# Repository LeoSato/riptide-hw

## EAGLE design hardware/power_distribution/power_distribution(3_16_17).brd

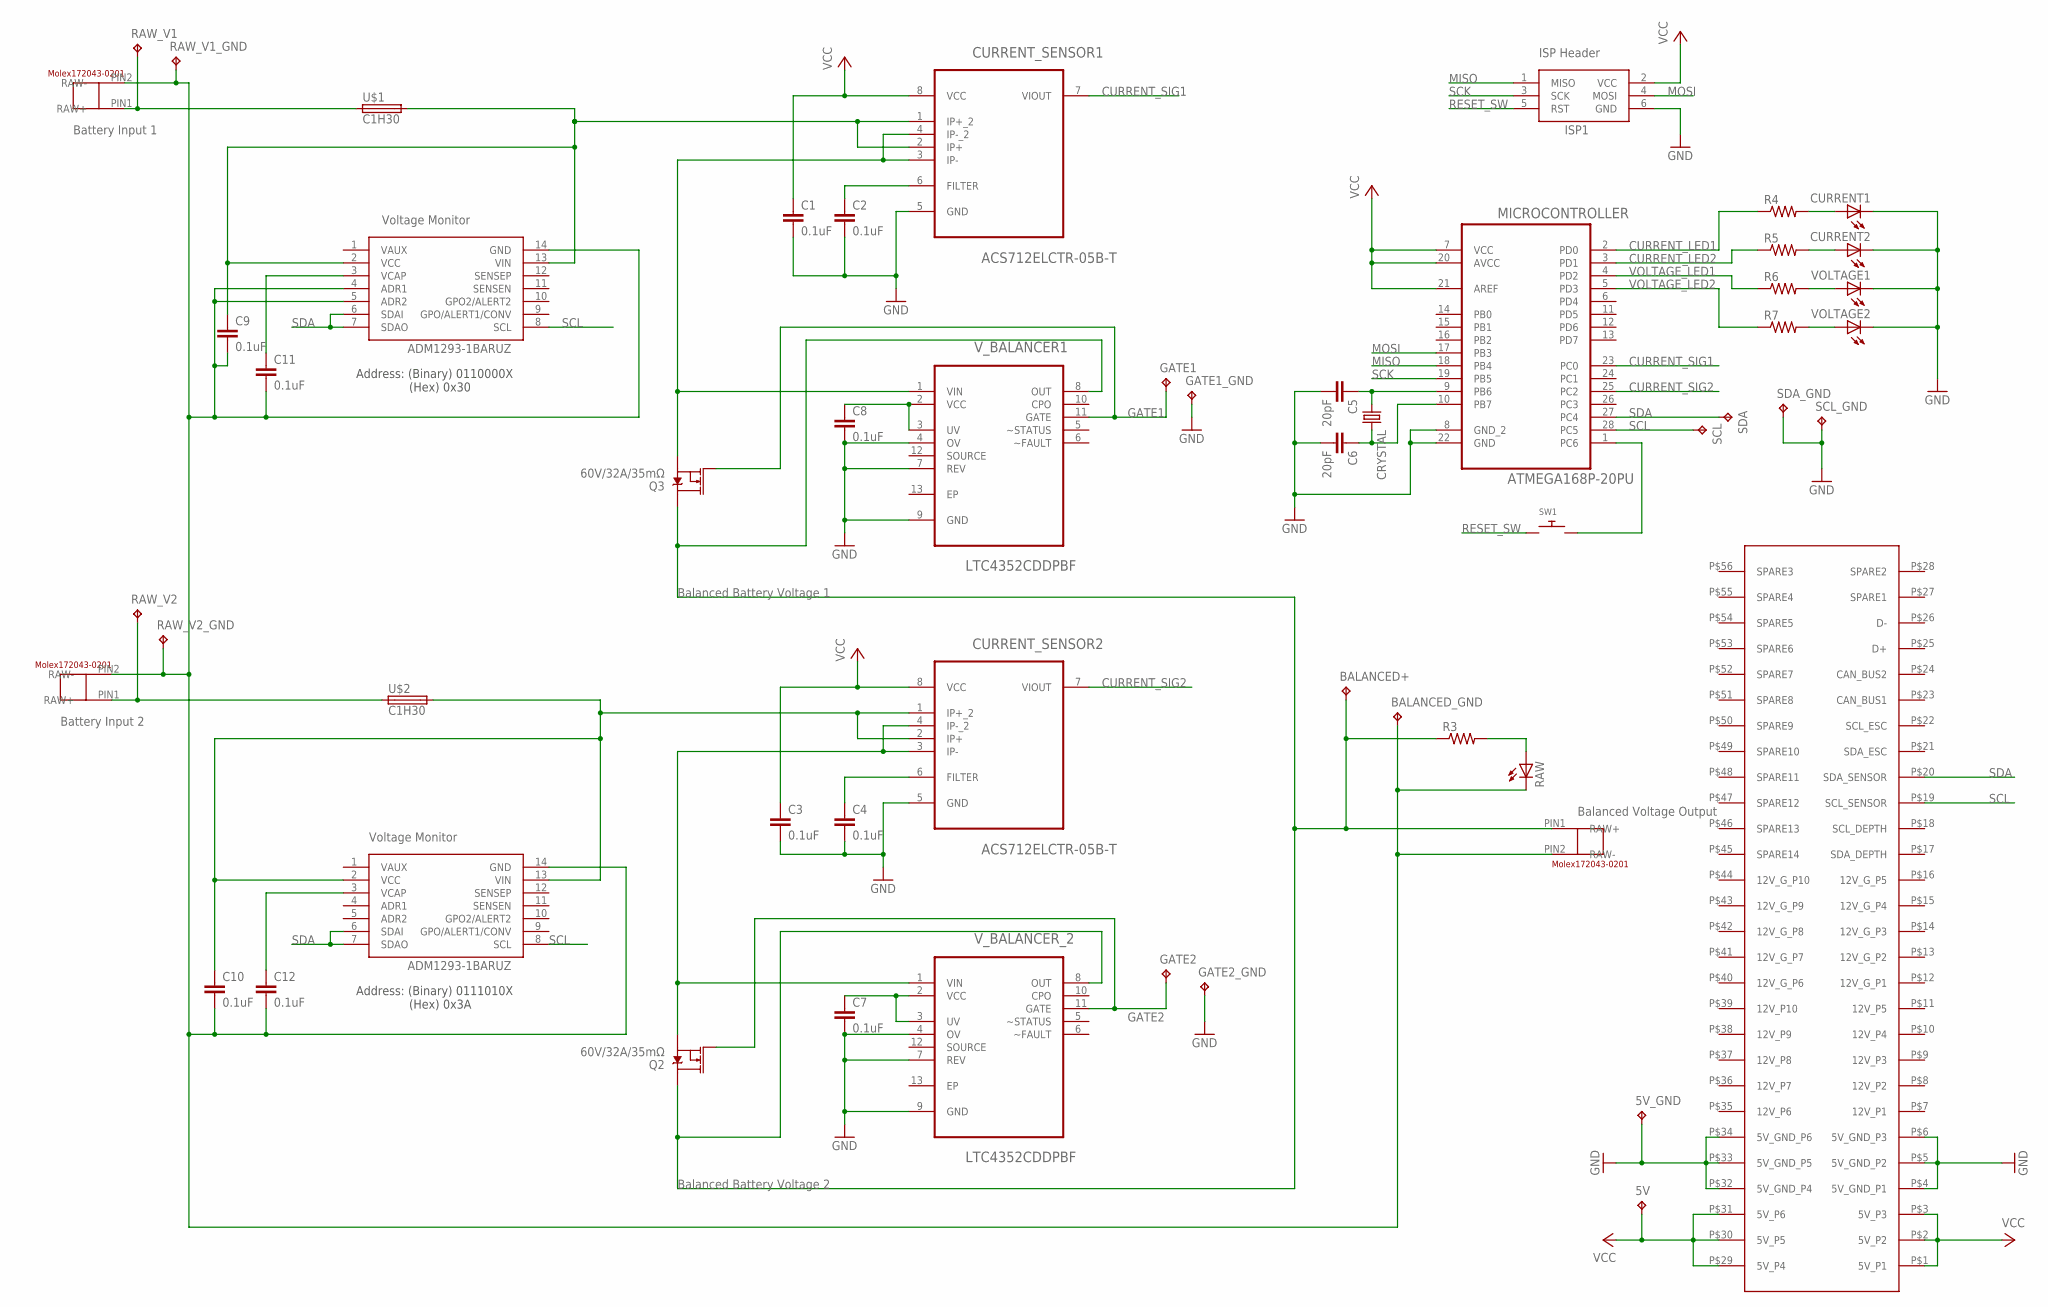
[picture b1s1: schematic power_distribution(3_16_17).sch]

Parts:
5V, 5V_GND: TPPAD1-13; P1-13
BALANCED+: TPPAD1-13; P1-13
BALANCED_GND: TPPAD1-13; P1-13
C1, C2, C3, C4, C7, C8, C9, C10, C11, C12: 0.1uF; CAP-PTH-SMALL-KIT
C5, C6: 20pF; CAP-PTH-SMALL-KIT
CRYSTAL: CRYSTALHC49U-V; HC49U-V
CURRENT1, CURRENT2: LED3MM
CURRENT_SENSOR1, CURRENT_SENSOR2: ACS712ELCTR-05B-T; SOIC127P600X175-8N
GATE1, GATE1_GND, GATE2, GATE2_GND: TPPAD1-13; P1-13
INPUT1, INPUT2: MOLEX172043-0201
ISP1: AVRISP-6; AVRISP
MICROCONTROLLER: ATMEGA168P-20PU; DIP254P762X457-28
OUTPUT: MOLEX172043-0201
Q2, Q3: 60V/32A/35mΩ; TO220V
R3, R4, R5, R6, R7: R-US_0207/12; 0207/12
RAW: LED3MM
RAW_V1, RAW_V1_GND, RAW_V2, RAW_V2_GND: TPPAD1-13; P1-13
SCL: TPPAD1-13; P1-13
SCL_GND: TPPAD1-13; P1-13
SDA: TPPAD1-13; P1-13
SDA_GND: TPPAD1-13; P1-13
SW1: SWITCH_PUSHBUTTONEVQ-PE; TACT_PANA-EVQ
U$1, U$2: C1H30
U$3: 1-530844-7
U$4, U$5: ADM1293; SOP65P640X120-14N
VOLTAGE1, VOLTAGE2: LED3MM
V_BALANCER1: LTC4352CDDPBF; DFN300X300X80-13N
V_BALANCER_2: LTC4352CDDPBF; DFN300X300X80-13N

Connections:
CURRENT_LED1: MICROCONTROLLER.2 (PD0), R4.1
CURRENT_LED2: MICROCONTROLLER.3 (PD1), R5.1
CURRENT_SIG1: CURRENT_SENSOR1.7 (VIOUT), MICROCONTROLLER.23 (PC0)
CURRENT_SIG2: CURRENT_SENSOR2.7 (VIOUT), MICROCONTROLLER.25 (PC2)
GATE1: GATE1.TP, Q3.1 (G), V_BALANCER1.11 (GATE)
GATE2: GATE2.TP, Q2.1 (G), V_BALANCER_2.11 (GATE)
GND: 5V_GND.TP, C1.2, C2.2, C3.2, C4.2, C5.2, C6.2, C7.2, C8.2, CURRENT1.K (C), CURRENT2.K (C), CURRENT_SENSOR1.5 (GND), CURRENT_SENSOR2.5 (GND), GATE1_GND.TP, GATE2_GND.TP, ISP1.6 (GND), MICROCONTROLLER.8 (GND_2), MICROCONTROLLER.22 (GND), SCL_GND.TP, SDA_GND.TP, U$3.P$4 (5V_GND_P1), U$3.P$5 (5V_GND_P2), U$3.P$6 (5V_GND_P3), U$3.P$32 (5V_GND_P4), U$3.P$33 (5V_GND_P5), U$3.P$34 (5V_GND_P6), VOLTAGE1.K (C), VOLTAGE2.K (C), V_BALANCER1.4 (OV), V_BALANCER1.7 (REV), V_BALANCER1.9 (GND), V_BALANCER_2.4 (OV), V_BALANCER_2.7 (REV), V_BALANCER_2.9 (GND)
MISO: ISP1.1 (MISO), MICROCONTROLLER.18 (PB4)
MOSI: ISP1.4 (MOSI), MICROCONTROLLER.17 (PB3)
unnamed: C9.1, CURRENT_SENSOR1.1 (IP+_2), CURRENT_SENSOR1.2 (IP+), U$1.P$2 (2), U$4.2 (VCC), U$4.13 (VIN)
unnamed: C5.1, CRYSTAL.1, MICROCONTROLLER.9 (PB6)
unnamed: C7.1, V_BALANCER_2.2 (VCC), V_BALANCER_2.3 (UV)
unnamed: C6.1, CRYSTAL.2, MICROCONTROLLER.10 (PB7)
unnamed: CURRENT_SENSOR1.3 (IP-), CURRENT_SENSOR1.4 (IP-_2), Q3.3 (S), V_BALANCER1.1 (VIN)
unnamed: CURRENT1.A, R4.2
unnamed: R3.2, RAW.A
unnamed: C8.1, V_BALANCER1.2 (VCC), V_BALANCER1.3 (UV)
unnamed: INPUT1.PIN1 (RAW+), RAW_V1.TP, U$1.P$1 (1)
unnamed: C10.1, CURRENT_SENSOR2.1 (IP+_2), CURRENT_SENSOR2.2 (IP+), U$2.P$2 (2), U$5.2 (VCC), U$5.13 (VIN)
unnamed: C11.1, U$4.3 (VCAP)
unnamed: CURRENT2.A, R5.2
unnamed: C2.1, CURRENT_SENSOR1.6 (FILTER)
unnamed: R6.2, VOLTAGE1.A
unnamed: INPUT2.PIN1 (RAW+), RAW_V2.TP, U$2.P$1 (1)
unnamed: R7.2, VOLTAGE2.A
unnamed: C4.1, CURRENT_SENSOR2.6 (FILTER)
unnamed: BALANCED_GND.TP, C9.2, C10.2, C11.2, C12.2, INPUT1.PIN2 (RAW-), INPUT2.PIN2 (RAW-), OUTPUT.PIN2 (RAW-), RAW.K (C), RAW_V1_GND.TP, RAW_V2_GND.TP, U$4.4 (ADR1), U$4.5 (ADR2), U$4.14 (GND), U$5.14 (GND)
unnamed: C12.1, U$5.3 (VCAP)
unnamed: BALANCED+.TP, OUTPUT.PIN1 (RAW+), Q2.2 (D), Q3.2 (D), R3.1, V_BALANCER1.8 (OUT), V_BALANCER_2.8 (OUT)
unnamed: MICROCONTROLLER.1 (PC6), SW1.P$2
RESET_SW: ISP1.5 (RST), SW1.P$1
SCK: ISP1.3 (SCK), MICROCONTROLLER.19 (PB5)
SCL: MICROCONTROLLER.28 (PC5), SCL.TP, U$3.P$19 (SCL_SENSOR), U$4.8 (SCL), U$5.8 (SCL)
SDA: MICROCONTROLLER.27 (PC4), SDA.TP, U$3.P$20 (SDA_SENSOR), U$4.6 (SDAI), U$4.7 (SDAO), U$5.6 (SDAI), U$5.7 (SDAO)
VCC: 5V.TP, C1.1, C3.1, CURRENT_SENSOR1.8 (VCC), CURRENT_SENSOR2.8 (VCC), ISP1.2 (VCC), MICROCONTROLLER.7 (VCC), MICROCONTROLLER.20 (AVCC), MICROCONTROLLER.21 (AREF), U$3.P$1 (5V_P1), U$3.P$2 (5V_P2), U$3.P$3 (5V_P3), U$3.P$29 (5V_P4), U$3.P$30 (5V_P5), U$3.P$31 (5V_P6)
VOLTAGE_IN2: CURRENT_SENSOR2.3 (IP-), CURRENT_SENSOR2.4 (IP-_2), Q2.3 (S), V_BALANCER_2.1 (VIN)
VOLTAGE_LED1: MICROCONTROLLER.4 (PD2), R6.1
VOLTAGE_LED2: MICROCONTROLLER.5 (PD3), R7.1

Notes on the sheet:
Voltage Monitor
ADM1293-1BARUZ
Address: (Binary) 0111010X (Hex) 0x3A
Address: (Binary) 0110000X (Hex) 0x30
Battery Input 1
Battery Input 2
Balanced Battery Voltage 1
Balanced Battery Voltage 2
Balanced Voltage Output
ISP Header

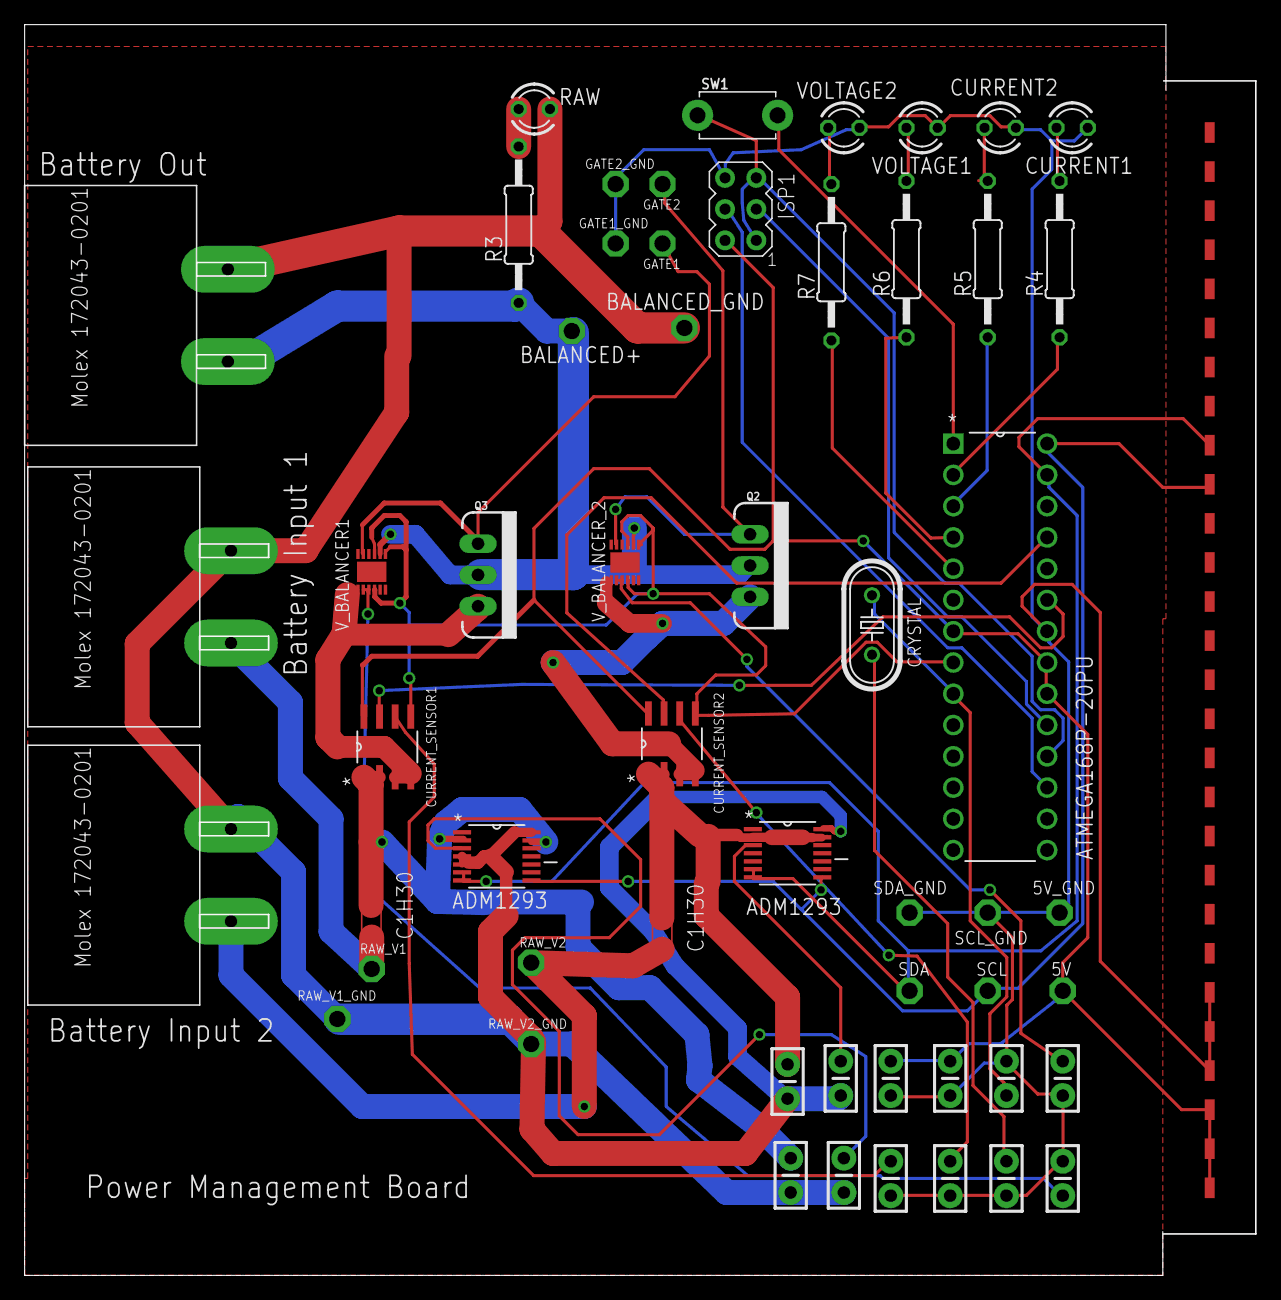
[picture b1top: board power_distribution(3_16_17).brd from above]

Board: 2 copper layers, 100.0 x 101.6 mm, 56 parts (0 on the bottom side), 38 nets.

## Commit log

2017-02-12 Balances battery voltages and outputs one combined voltage
2017-02-22 Moved Molex Connectors To The Top Of The Board
2017-02-22 Moved molex connectors to the top and put in silk screen
2017-02-22 Moved molex connectors to the top and placed silk screen
2017-03-16 Some missing connections between the crystal and ATMEGA were added

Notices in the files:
parts and their libraries:
SparkFun-Capacitors: Licensing: Creative Commons ShareAlike 4.0 International - https://creativecommons.org/licenses/by-sa/4.0
